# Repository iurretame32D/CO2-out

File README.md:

# CO2-OUT
Iurreta LHI ikastetxeko Mantentze-lan elektronikoa heziketa zikloko ikasleek proiektu moduluan egindako lana: CO2, hezetasuna eta tenperatura neurtu eta Lora bitarez TheThingsNetworkera bidali. NodeRed erabiliz datuak erakutsi.

Iurreta Electronic Vocational Training student project: measurement of CO2, humidity and temperature. LORA TTN Communications. Dashboard via NodeRed.

## The Things Network gateway

## Bloke Diagrama / Block diagram 

## Emaitzak / Result

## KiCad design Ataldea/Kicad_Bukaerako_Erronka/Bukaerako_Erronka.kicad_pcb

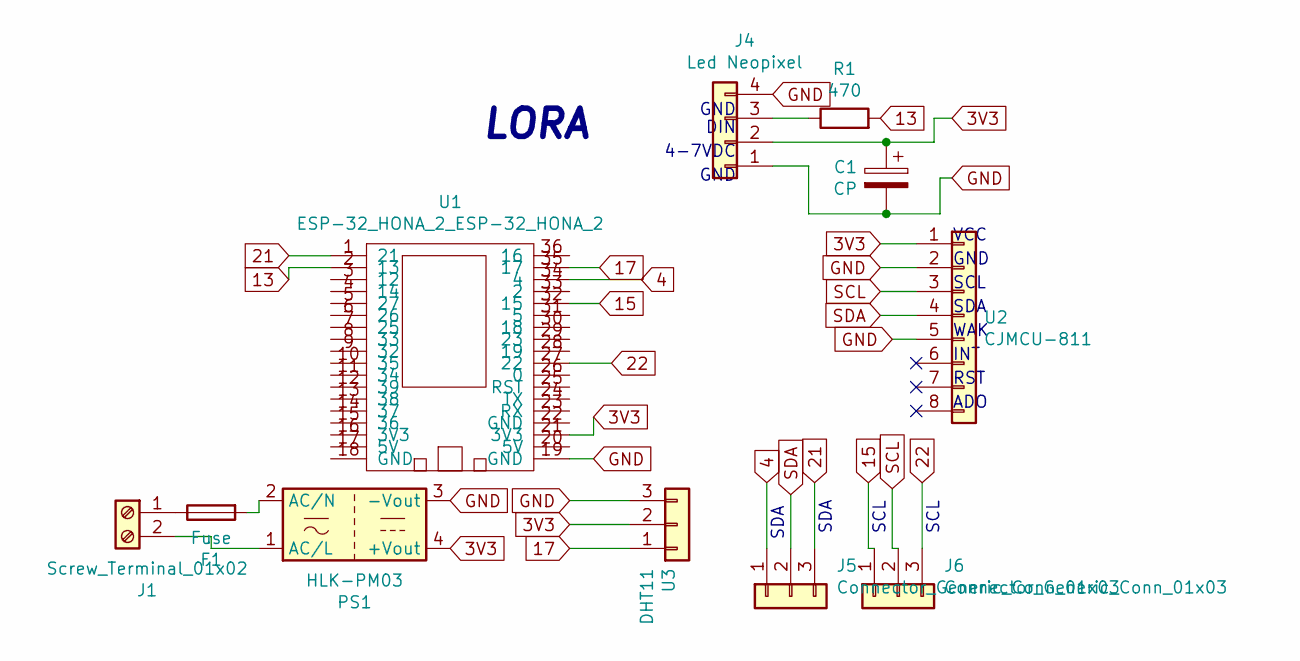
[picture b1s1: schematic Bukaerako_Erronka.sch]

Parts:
C1: CP; CP_Radial_D10.0mm_P3.80mm
F1: Fuse; Fuseholder_Cylinder-5x20mm_Stelvio-Kontek_PTF78_Horizontal_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
J1: Screw_Terminal_01x02; TerminalBlock_bornier-2_P5.08mm
J4: Led Neopixel; PinSocket_1x04_P2.54mm_Vertical
J5, J6: Connector_Generic_Conn_01x03; PinSocket_1x03_P2.54mm_Vertical
PS1: HLK-PM03; Converter_ACDC_HiLink_HLK-PMxx
R1: 470; R_Axial_DIN0207_L6.3mm_D2.5mm_P7.62mm_Horizontal
U1: ESP-32_HONA_2_ESP-32_HONA_2; ESP_32_HONA_V3
U2: CJMCU-811; PinSocket_1x08_P2.54mm_Vertical
U3: DHT11; PinSocket_1x03_P2.54mm_Vertical

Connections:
3V3: C1.1, J4.2, PS1.4 (+Vout), U1.21 (3V3), U2.1, U3.2
4: J5.1, U1.34 (4)
13: R1.2, U1.2 (13)
15: J6.1, U1.32 (15)
17: U1.35 (17), U3.1
21: J5.3, U1.1 (21)
22: J6.3, U1.27 (22)
GND: C1.2, J4.1, J4.4, PS1.3 (-Vout), U1.19 (GND), U2.2, U2.5, U3.3
unnamed: F1.1, J1.1
unnamed: F1.2, PS1.2 (AC/N)
unnamed: J1.2, PS1.1 (AC/L)
unnamed: J4.3, R1.1
SCL: J6.2, U2.3
SDA: J5.2, U2.4

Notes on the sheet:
VCC
GND
SCL
SDA
WAK
INT
RST
ADO
LORA
DIN
4-7VDC

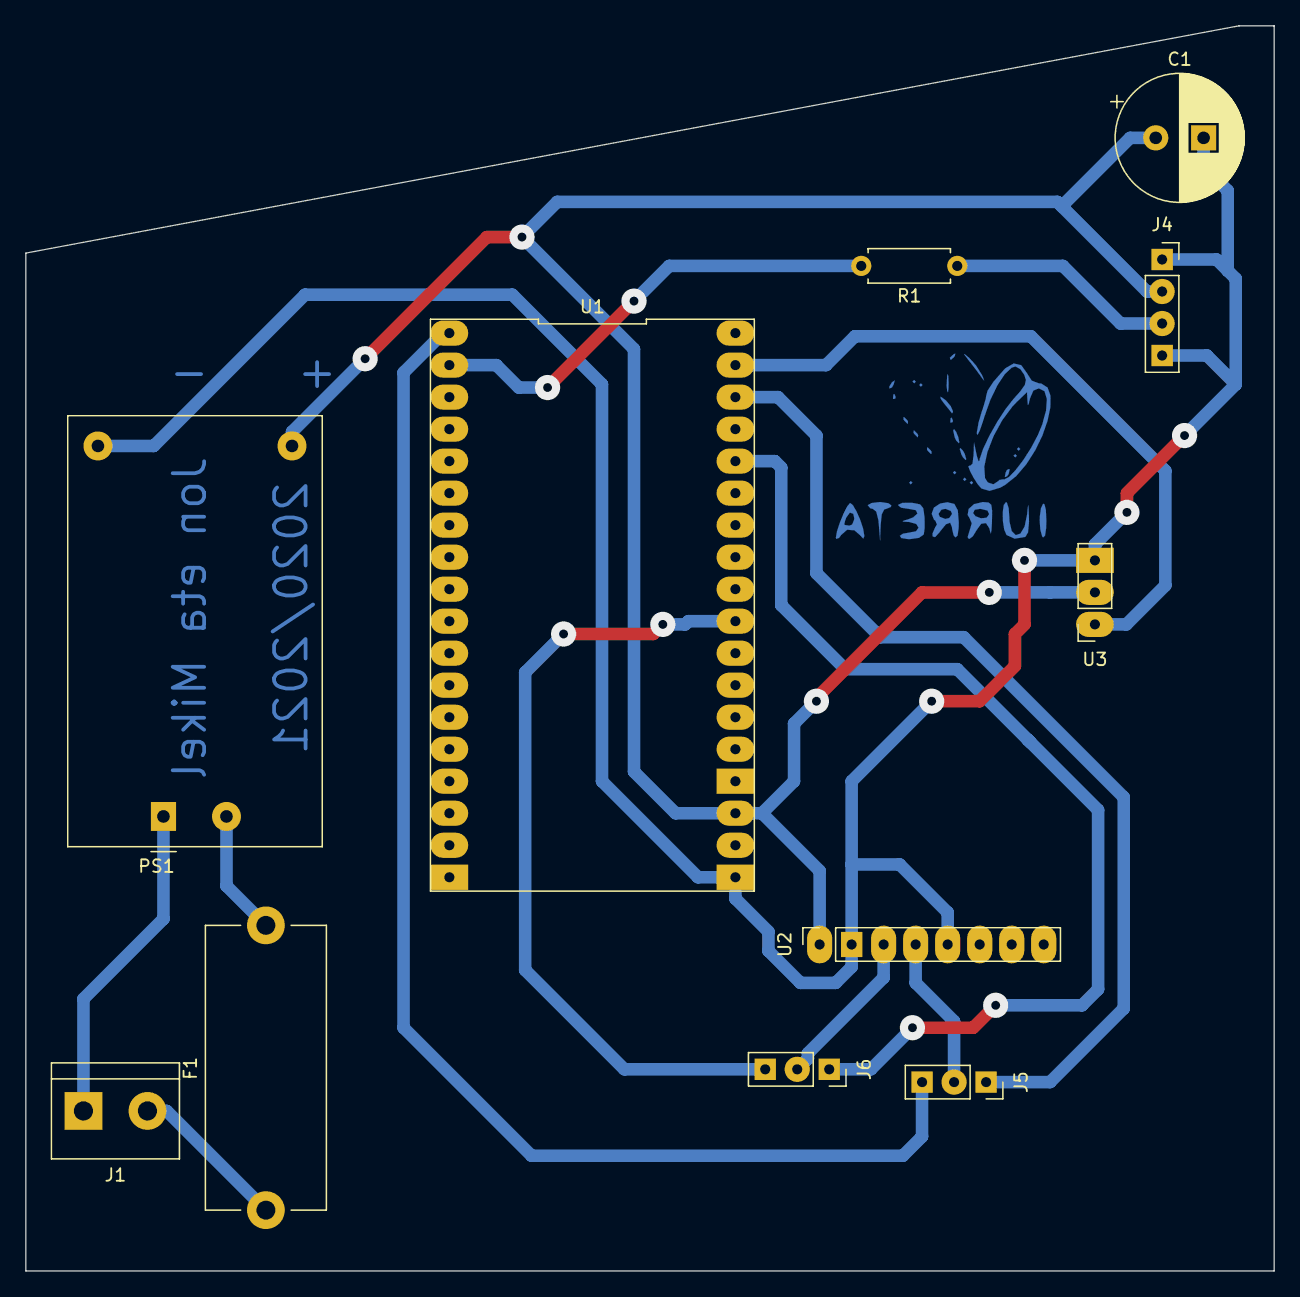
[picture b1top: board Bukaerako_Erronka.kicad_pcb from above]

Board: 2 copper layers, 99.1 x 98.8 mm, 11 parts (0 on the bottom side), 14 nets.

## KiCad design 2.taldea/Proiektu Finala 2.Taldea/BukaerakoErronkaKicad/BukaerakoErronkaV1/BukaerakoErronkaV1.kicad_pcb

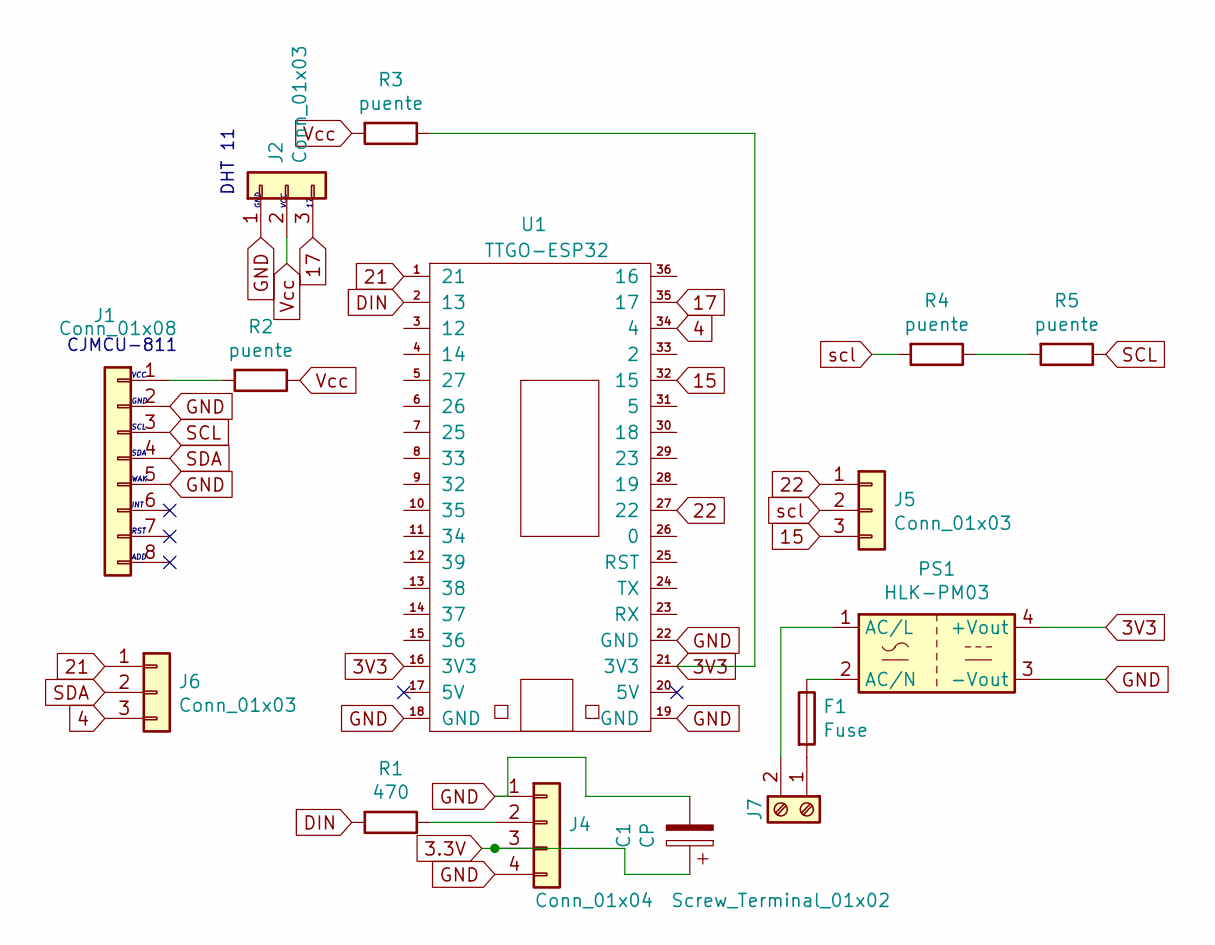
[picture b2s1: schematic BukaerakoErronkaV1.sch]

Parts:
C1: CP; CP_Radial_D10.0mm_P3.80mm
F1: Fuse; Fuseholder_Cylinder-5x20mm_Stelvio-Kontek_PTF78_Horizontal_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
J1: Conn_01x08; JST_EH_B8B-EH-A_1x08_P2.50mm_Vertical
J2, J5, J6: Conn_01x03; JST_EH_B3B-EH-A_1x03_P2.50mm_Vertical
J4: Conn_01x04; JST_EH_B4B-EH-A_1x04_P2.50mm_Vertical
J7: Screw_Terminal_01x02; TerminalBlock_bornier-2_P5.08mm
PS1: HLK-PM03; Converter_ACDC_HiLink_HLK-PMxx
R1: 470; R_Axial_DIN0207_L6.3mm_D2.5mm_P7.62mm_Horizontal
R2: puente; R_Axial_DIN0207_L6.3mm_D2.5mm_P15.24mm_Horizontal
R3, R4, R5: puente; R_Axial_DIN0207_L6.3mm_D2.5mm_P7.62mm_Horizontal
U1: TTGO-ESP32

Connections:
3.3V: C1.1, J4.3
3V3: PS1.4 (+Vout), R3.1, U1.16 (3V3), U1.21 (3V3)
4: J6.3, U1.34 (4)
15: J5.3, U1.32 (15)
17: J2.3, U1.35 (17)
21: J6.1, U1.1 (21)
22: J5.1, U1.27 (22)
DIN: R1.2, U1.2 (13)
GND: C1.2, J1.2, J1.5, J2.1, J4.1, J4.4, PS1.3 (-Vout), U1.18 (GND), U1.19 (GND), U1.22 (GND)
unnamed: F1.1, PS1.2 (AC/N)
unnamed: F1.2, J7.1
unnamed: J1.1, R2.2
unnamed: J4.2, R1.1
unnamed: J7.2, PS1.1 (AC/L)
unnamed: R4.1, R5.2
SCL: J1.3, R5.1
SDA: J1.4, J6.2
Vcc: J2.2, R2.1, R3.2
scl: J5.2, R4.2

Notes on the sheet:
DHT 11
CJMCU-811
VCC
GND
SCL
SDA
WAK
INT
RST
ADD

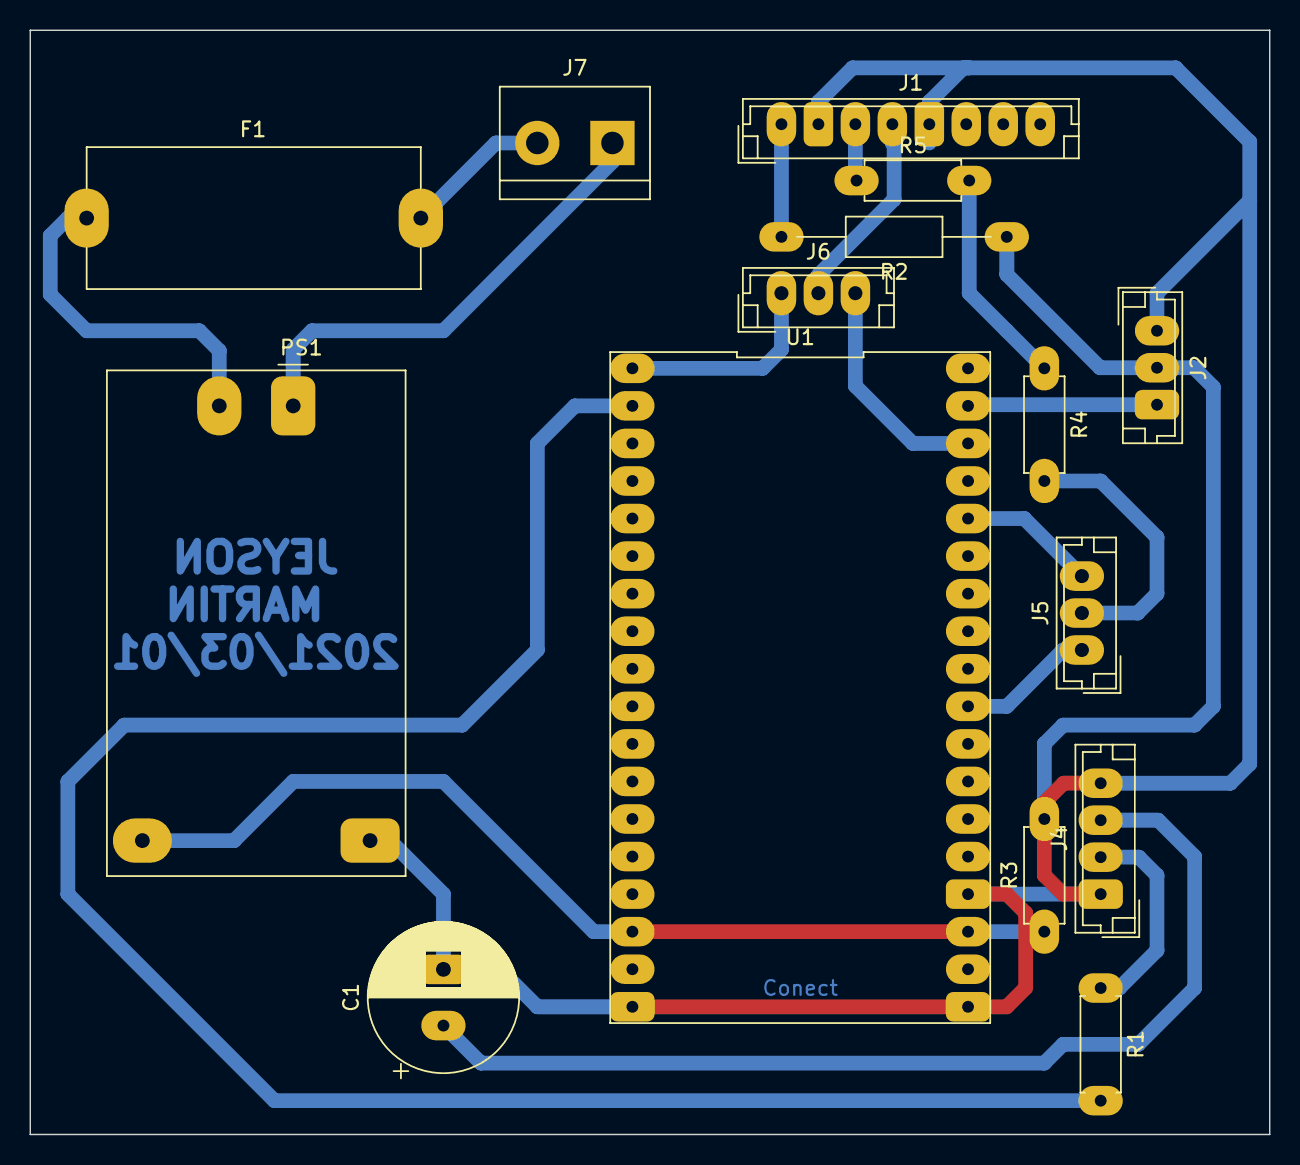
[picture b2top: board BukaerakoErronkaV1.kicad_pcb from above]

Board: 2 copper layers, 83.8 x 74.7 mm, 15 parts (0 on the bottom side), 19 nets.

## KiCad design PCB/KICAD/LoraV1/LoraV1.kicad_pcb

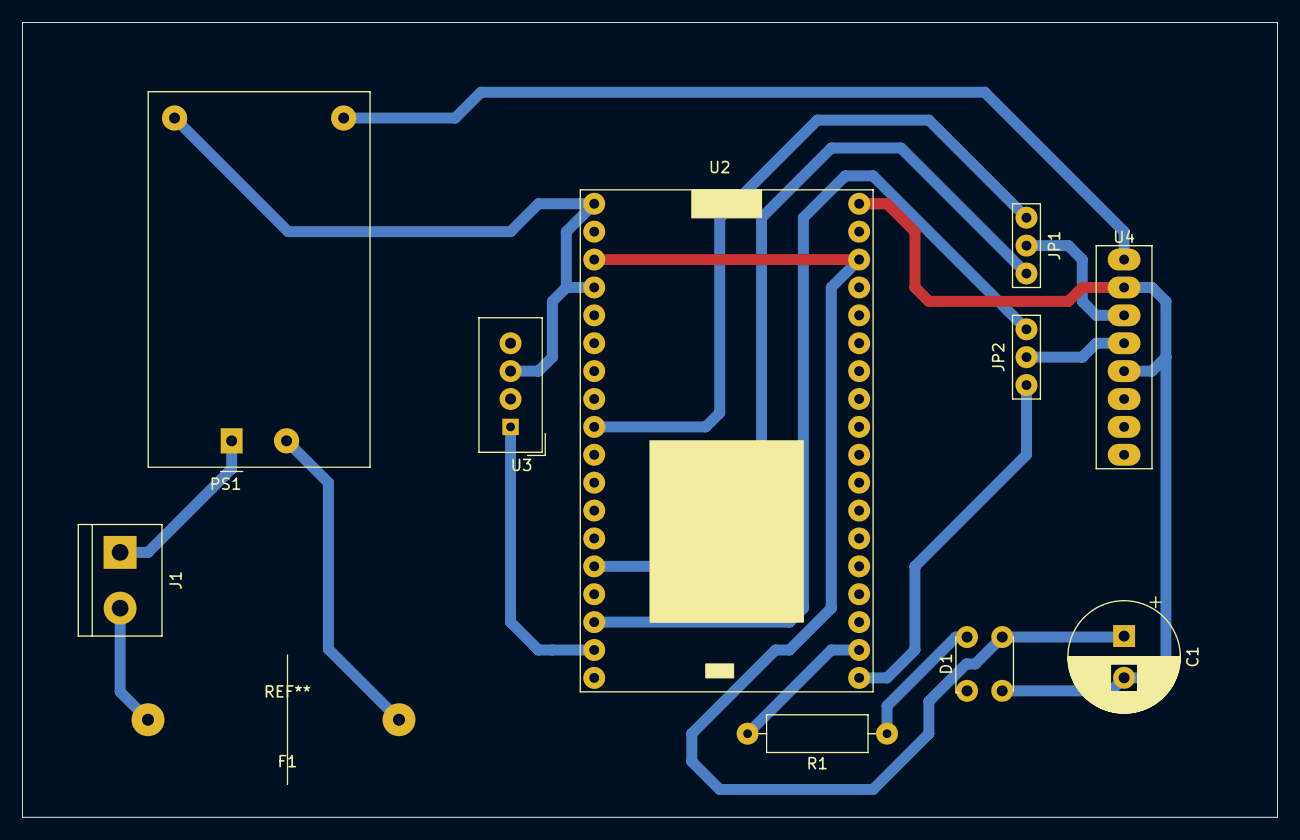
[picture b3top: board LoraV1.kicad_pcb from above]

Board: 2 copper layers, 114.3 x 72.4 mm, 11 parts (0 on the bottom side), 16 nets.

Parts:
C1: CP; CP_Radial_D10.0mm_P3.80mm
D1: NeoPixel_THT; LED_Inolux_IN-PI554FCH_PLCC4_5.0x5.0mm_P3.2mm
F1: Fuse; fusiblea
J1: Conn_01x02; TerminalBlock_bornier-2_P5.08mm
JP1, JP2: Jumper_NC_Dual; jumperxabi
PS1: HLK-PM03; Converter_ACDC_HiLink_HLK-PMxx
R1: 470; R_Axial_DIN0309_L9.0mm_D3.2mm_P12.70mm_Horizontal
U2: TTGO; ESP32
U3: DHT11; Aosong_DHT11_5.5x12.0_P2.54mm
U4: RJCMU-811

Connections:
unnamed: C1.1, D1.3, U2.51
unnamed: C1.2, D1.2, U2.52, U4.2, U4.5
unnamed: D1.4, R1.1
unnamed: F1.1, PS1.2
unnamed: F1.2, J1.2
unnamed: J1.1, PS1.1
unnamed: JP1.1, U2.22
unnamed: JP1.2, U4.3
unnamed: JP1.3, U2.15
unnamed: JP2.1, U2.21
unnamed: JP2.2, U4.4
unnamed: JP2.3, U2.4
unnamed: PS1.3, U2.50, U3.3
unnamed: PS1.4, U4.1
unnamed: R1.2, U2.13
unnamed: U2.17, U3.1

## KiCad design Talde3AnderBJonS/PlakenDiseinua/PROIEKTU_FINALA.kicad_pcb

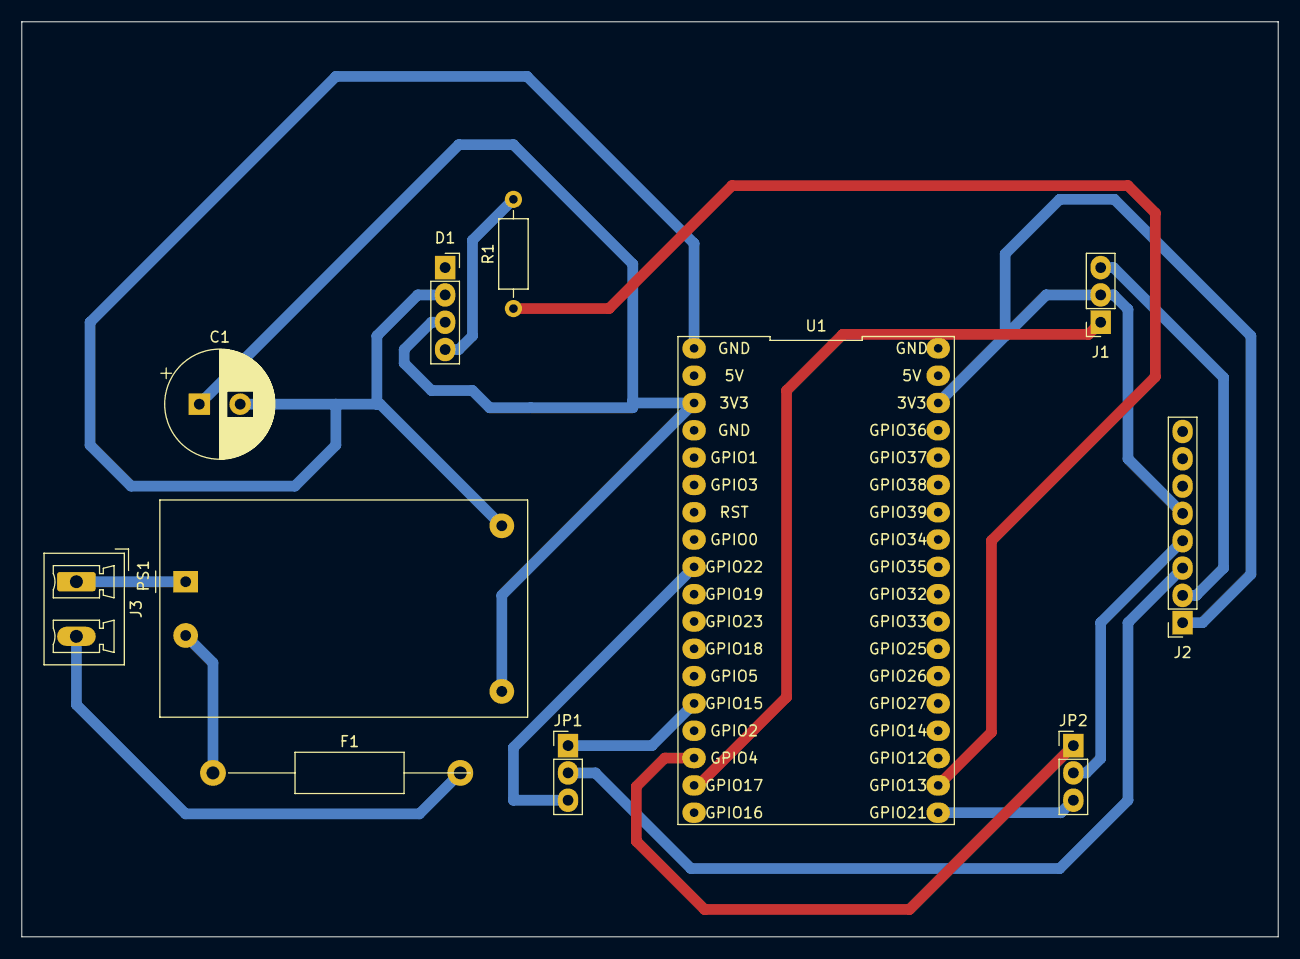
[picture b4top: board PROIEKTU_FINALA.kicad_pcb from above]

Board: 2 copper layers, 116.8 x 85.1 mm, 11 parts (0 on the bottom side), 16 nets.

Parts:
C1: CP; CP_Radial_D10.0mm_P3.80mm
D1: NeoPixel_THT; PinSocket_1x04_P2.54mm_Vertical
F1: Fuse; R_Axial_DIN0411_L9.9mm_D3.6mm_P25.40mm_Horizontal
J1: Conn_01x03; PinSocket_1x03_P2.54mm_Vertical
J2: Conn_01x08; PinSocket_1x08_P2.54mm_Vertical
J3: Conn_01x02_Male; PhoenixContact_MCV_1,5_2-G-5.08_1x02_P5.08mm_Vertical
JP1, JP2: Jumper_3_Open; PinHeader_1x03_P2.54mm_Vertical
PS1: HLK-PM01; Converter_ACDC_HiLink_HLK-PMxx
R1: R; R_Axial_DIN0207_L6.3mm_D2.5mm_P10.16mm_Horizontal
U1: TTGO-ESP32; TTGO_ESP32

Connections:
unnamed: C1.1, D1.3, PS1.4, U1.3V3
unnamed: C1.2, D1.1, D1.2, PS1.3, U1.GND
unnamed: D1.4, R1.2
unnamed: F1.1, PS1.2
unnamed: F1.2, J3.2
unnamed: J1.1, U1.17
unnamed: J1.2, J2.1, J2.5
unnamed: J1.3, J2.2
unnamed: J2.3, JP1.2
unnamed: J2.4, JP2.2
unnamed: J3.1, PS1.1
unnamed: JP1.1, U1.15
unnamed: JP1.3, U1.22
unnamed: JP2.1, U1.4
unnamed: JP2.3, U1.21
unnamed: R1.1, U1.13

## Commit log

2021-03-05 Add files via upload
    u
2021-03-05 Add files via upload
    .
2021-03-05 Add files via upload
    Taldea3AnderBJonS
